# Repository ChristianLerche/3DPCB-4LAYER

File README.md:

# 3DPCB-4LAYER
Placeholder - don't use

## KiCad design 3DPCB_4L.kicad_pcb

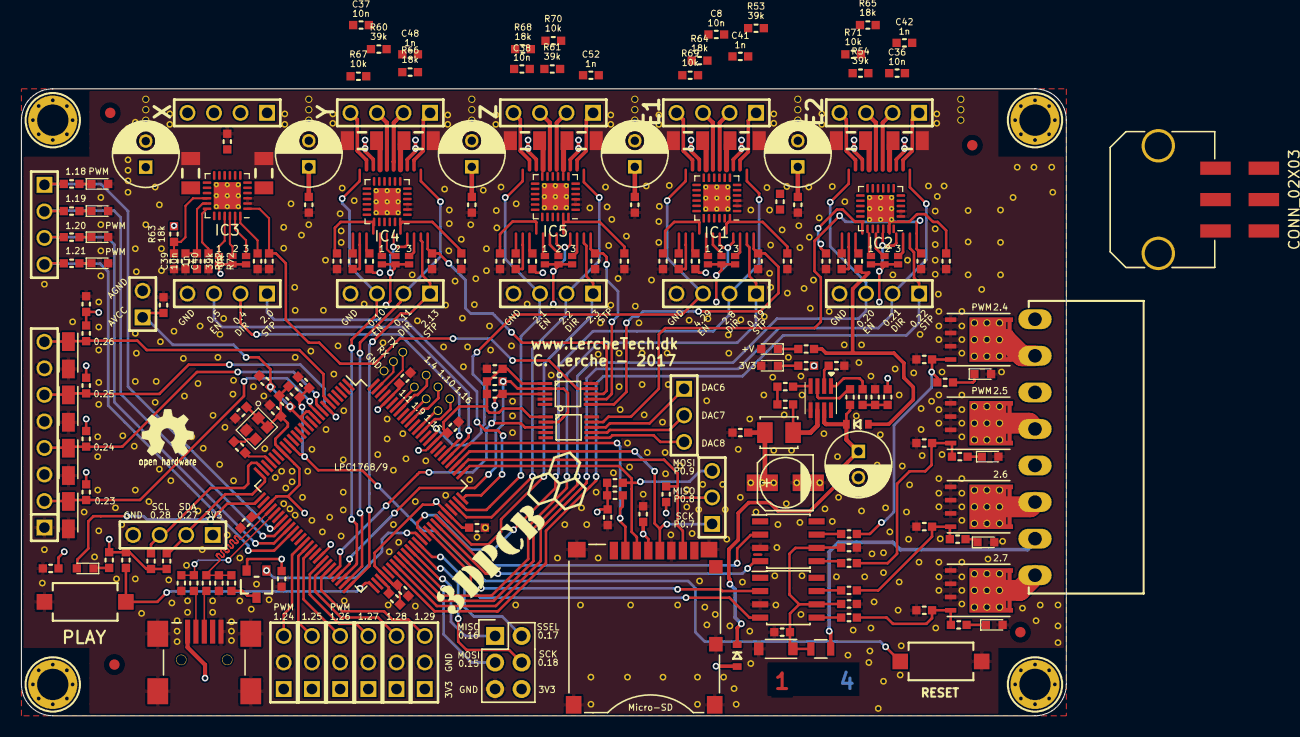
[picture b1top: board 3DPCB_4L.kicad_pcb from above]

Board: 4 copper layers, 100.0 x 60.0 mm, 224 parts (0 on the bottom side), 176 nets.

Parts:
C1, C2, C6, C12, C13, C14, C15, C16, C17, C19, C20, C21, C22, C23, C28, C29, C30, C31, C32, C33, C34, C35, C44, C45, C46, C47, C50, C51, C52, C53, C54, C64, C65, C67, C69, C71: 100n; Lerche_C0603
C3, C4, C7, C10: 10uF; TantalC_SizeA_EIA-3216_Reflow
C5, C9: 18p; Lerche_C0603
C8, C36, C37: 100nF; Lerche_C0603
C8#2, C36#2, C37#2, C38, C38#2, C39: 10n; Lerche_C0603
C11, C24, C25, C26, C27, C70: 100uF; C_Radial_D6.3_L11.2_P2.5
C18: 100pF; Lerche_C0603
C40, C41#2, C42#2, C48#2, C52#2: 1n; Lerche_C0603
C41, C42, C48, C55: 220n; Lerche_C0603
C43: 47uF; c_elec_5x5.8
C49: 1uF; Lerche_C0603
CONN1: USB_MINI; Lerche_MINI_USB
D1, D2, D3, D4, D6, D7, D8, D11, D12, D13, D14: LED; LED_0603
D5, D9: DIODESCH; Lerche_SOD323
D10: Vz10V/0.5W; SOD-123
FID1, FID2, FID3, FID4: FIDUCIAL; Lerche_Fiducial
IC1, IC2, IC3, IC4, IC5: STSPIN820; QFN-24-1EP_4x4mm_P0.5mm_EP2.6x2.6mm_ThermalVias
IC6: MP9943; Lerche_MP9943
J2, J3, J4, J5, J6, J7, J8, J9, J10, J11, J12, J13, J14, J15, J16: Lerche_2PsolderJumper
K1, K2, K3, K4, K5, K6, K8, K9: CONN_3; Lerche_3P_2.54mm
K7: CONN_3; Lerche_3P_1.27MM
L1: INDUCTOR; Lerche_R0603
L2: IHLP1212BZER2R2M11; Lerche_IHLP-1212BZ-11_Inductor
OSC1: QX2; Lerche_Oscillator_2.5x2.0mm
P1: CONN_8; Lerche_8P_2.54mm
P2: CONN_8; Lerche_8P_CONN_3,5mm
P3: CONN_01X02; Lerche_2P_2.54mm
P5, P6, P7, P9, P13: CONN_4; Lerche_4P_2.54mm
P8: CONN_02X03; Lerche_Molex_Microfit_0430450607
P11: CONN_3X2; Pin_Header_Straight_2x03
P12: CONN_3X2; Lerche_6P_1.6mm_2ROW
R1, R9, R18, R19, R25, R27, R41, R42, R43, R67, R69, R70, R71: 10k; Lerche_R0603
R2, R3, R4, R5, R6, R28: 1k; Lerche_R0603
R7, R8: 33R; Lerche_R0603
R10, R12, R13, R34: 4K7; Lerche_R0603
R11: 1k5; Lerche_R0603
R14, R15, R16, R20: 47k; Lerche_R0603
R17: 1k; R_0805
R21, R22, R23, R24, R29, R30, R31, R32, R33, R37: 0R05; Lerche_R1206
R26, R46, R47, R48, R72: 0R; Lerche_R0603
R35: 1M; Lerche_R0603
R36: 20R; Lerche_R0603
R38: 51k; Lerche_R0603
R39: 13k; Lerche_R0603
R40: 41k2; Lerche_R0603
R44, R45: 3k3; Lerche_R0603
R49, R50, R51, R52: 4k7; Lerche_R0603
R53, R54, R60, R61, R62: 39k; Lerche_R0603
R55: 5k8; Lerche_R0603
R56, R57, R58, R59: 10R; Lerche_R0603
R63, R64, R65, R66, R68: 18k; Lerche_R0603
U1, U4, U13, U16, U21, U22, U25: CONN_4_LERCHE; Lerche_4P_2.54mm
U2, U15: SPST_MOMENTARY; Lerche_SPST_ITEAD
U3: BSS84; Lerche_SOT23-3
U5, U7, U8, U24: IRFH5302; Lerche_PQFN_5x6B
U6: LPC1768_TQFP100; TQFP-100_14x14mm_Pitch0.5mm
U9, U11: TC4427; SOIC-8_3.9x4.9mm_Pitch1.27mm
U10: MICRO-SD; Lerche_Molex_502774-0891
U12, U23: MCP4728; Lerche_MSOP-10

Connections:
+3.3V: C6.1, C12.1, C13.1, C14.1, C15.1, C16.1, C19.2, C22.1, C23.1, C43.1, C44.1, C45.1, C46.1, C50.1, C64.1, J2.1, J3.1, J4.1, J5.1, J6.1, J7.1, J8.1, J9.1, J10.1, J11.1, J12.1, J13.1, J14.1, J15.1, J16.1, K1.1, K2.1, K3.1, K4.1, K5.1, K6.1, L1.1, L2.2, OSC1.1, OSC1.4, P11.6, R1.1, R2.1, R9.1, R10.1, R12.1, R13.1, R18.2, R19.2, R27.1, R28.1, R34.1, R40.1, R41.1, R42.1, R43.1, R44.1, R45.1, R63.2, R64.2, R65.2, R66.2, R68.2, U3.2, U6.19, U6.28, U6.42, U6.54, U6.71, U6.84, U6.96, U10.4, U12.1, U16.1, U23.1
+12V: C24.1, C25.1, C26.1, C27.1, C28.1, C29.1, C30.1, C31.1, C52.1, C53.1, C54.1, C69.1, C70.1, C71.1, D9.1, IC1.9, IC1.10, IC2.9, IC2.10, IC3.9, IC3.10, IC5.9, IC5.10, P8.2, R55.1
/P2.6_FET: P2.3, U8.3
/P2.7_FET: P2.1, U24.3
/PWM0_FET: P2.7, U5.3
/PWM1_FET: P2.5, U7.3
DAC_SCL: R19.1, U6.47, U12.2, U23.2
DAC_SDA: R18.1, U6.46, U12.3, U23.3
DIR1: IC3.20, U1.2, U6.81
DIR2: IC4.20, U6.49, U21.2
DIR3: IC5.20, U6.73, U22.2
DIR4: IC1.20, U6.65, U25.2
DIR5: IC2.20, U6.57, U13.2
EN1: R62.2, U1.3, U6.80
EN2: R60.2, U6.48, U21.3
EN3: R61.2, U6.74, U22.3
EN4: R53.2, U6.85, U25.3
EN5: R54.2, U6.58, U13.3
GND: C1.2, C2.2, C3.2, C4.2, C5.2, C6.2, C7.2, C8#2.2, C9.2, C10.2, C11.2, C12.2, C13.2, C14.2, C15.2, C16.2, C17.2, C19.1, C21.2, C22.2, C23.2, C24.2, C25.2, C26.2, C27.2, C28.2, C29.2, C30.2, C31.2, C32.2, C33.2, C34.2, C35.2, C36#2.2, C37#2.2, C38#2.2, C39.2, C40.1, C41.2, C41#2.1, C42.2, C42#2.1, C43.2, C44.2, C45.2, C46.2, C47.2, C48.2, C48#2.1, C49.2, C50.2, C51.2, C52#2.1, C55.2, C64.2, C65.2, C70.2, C71.2, CONN1.5, CONN1.Shie, D1.2, D2.2, D3.2, D4.2, D7.2, D8.2, D10.2, D11.2, D12.2, D13.2, D14.2, IC1.2, IC1.3, IC1.25, IC2.2, IC2.3, IC2.25, IC3.2, IC3.3, IC3.25, IC4.2, IC4.3, IC4.25, IC5.2, IC5.3, IC5.25, IC6.5, K1.2, K2.2, K3.2, K4.2, K5.2, K6.2, K7.3, OSC1.2, P1.1, P1.3, P1.5, P1.7, P3.2, P8.1, P8.4, P8.6, P11.5, R14.2, R15.2, R16.2, R20.2, R21.2, R22.2, R23.2, R24.2, R25.2, R26.2, R29.2, R30.2, R31.2, R32.2, R33.2, R37.2, R39.2, R46.2, R47.2, R48.2, R67.2, R69.2, R70.2, R71.2, R72.2, U1.4, U2.2, U5.2, U6.11, U6.15, U6.31, U6.41, U6.55, U6.72, U6.83, U6.97, U7.2, U8.2, U9.3, U10.6, U10.10, U10.11, U10.12, U10.13, U10.14, U11.3, U12.4, U12.10, U13.4, U15.2, U16.4, U21.4, U22.4, U23.4, U23.10, U24.2, U25.4
LED1: R3.2, U4.1, U6.32
LED2: R4.2, U4.2, U6.33
LED3: R5.2, U4.3, U6.34
LED4: R6.2, U4.4, U6.35
MISO1: P11.1, U6.61
MOSI1: P11.3, U6.60
MOSVCC: C21.1, C47.1, C49.1, D10.1, R17.2, U11.6
unnamed: C2.1, IC6.2
unnamed: C8.1, C8#2.1, IC1.17, R53.1
unnamed: C17.1, C35.1, L1.2, P3.1, U6.10, U6.12
unnamed: C18.1, OSC1.3
unnamed: C18.2, U6.22
unnamed: C20.1, R36.2
unnamed: C20.2, IC6.6, L2.1
unnamed: C36.1, C36#2.1, IC2.17, R54.1
unnamed: C37.1, C37#2.1, IC4.17, R60.1
unnamed: C38.1, C38#2.1, IC5.17, R61.1
unnamed: C39.1, IC3.17, R62.1
unnamed: C40.2, IC3.16, R63.1
unnamed: C41#2.2, IC1.16, R64.1
unnamed: C42#2.2, IC2.16, R65.1
unnamed: C48#2.2, IC4.16, R66.1
unnamed: C52.2, C52#2.2, IC5.16, R68.1
unnamed: CONN1.1, D5.1
unnamed: CONN1.2, R7.1
unnamed: CONN1.3, R8.1
unnamed: D1.1, R3.1
unnamed: D2.1, R4.1
unnamed: D3.1, R5.1
unnamed: D4.1, R6.1
unnamed: D6.1, R28.2
unnamed: D7.1, R2.2
unnamed: D8.1, R55.2
unnamed: D11.1, R50.2
unnamed: D12.1, R52.2
unnamed: D13.1, R49.2
unnamed: D14.1, R51.2
unnamed: IC1.4, IC1.5, IC1.6, R23.1
unnamed: IC1.7, P7.1
unnamed: IC1.8, P7.2
unnamed: IC1.11, P7.3
unnamed: IC1.12, P7.4
unnamed: IC1.13, IC1.14, IC1.15, R30.1
unnamed: IC1.18, R46.1
unnamed: IC1.21, J11.2
unnamed: IC1.22, J12.2
unnamed: IC1.23, J13.2
unnamed: IC1.24, R69.1
unnamed: IC2.4, IC2.5, IC2.6, R31.1
unnamed: IC2.7, P13.1
unnamed: IC2.8, P13.2
unnamed: IC2.11, P13.3
unnamed: IC2.12, P13.4
unnamed: IC2.13, IC2.14, IC2.15, R32.1
unnamed: IC2.18, R47.1
unnamed: IC2.21, J14.2
unnamed: IC2.22, J15.2
unnamed: IC2.23, J16.2
unnamed: IC2.24, R71.1
unnamed: IC3.4, IC3.5, IC3.6, R33.1
unnamed: IC3.7, P9.1
unnamed: IC3.8, P9.2
unnamed: IC3.11, P9.3
unnamed: IC3.12, P9.4
unnamed: IC3.13, IC3.14, IC3.15, R37.1
unnamed: IC3.18, R72.1
unnamed: IC3.21, J2.2
unnamed: IC3.22, J3.2
unnamed: IC3.23, J4.2
unnamed: IC3.24, R25.1
unnamed: IC4.4, IC4.5, IC4.6, R21.1
unnamed: IC4.7, P5.1
unnamed: IC4.8, P5.2
unnamed: IC4.11, P5.3
unnamed: IC4.12, P5.4
unnamed: IC4.13, IC4.14, IC4.15, R24.1
unnamed: IC4.18, R48.1
unnamed: IC4.21, J5.2
unnamed: IC4.22, J6.2
unnamed: IC4.23, J7.2
unnamed: IC4.24, R67.1
unnamed: IC5.4, IC5.5, IC5.6, R22.1
unnamed: IC5.7, P6.1
unnamed: IC5.8, P6.2
unnamed: IC5.11, P6.3
unnamed: IC5.12, P6.4
unnamed: IC5.13, IC5.14, IC5.15, R29.1
unnamed: IC5.18, R26.1
unnamed: IC5.21, J8.2
unnamed: IC5.22, J9.2
unnamed: IC5.23, J10.2
unnamed: IC5.24, R70.1
unnamed: IC6.1, R38.1
unnamed: IC6.3, R35.1
unnamed: IC6.4, R36.1
unnamed: R11.1, U3.3
unnamed: R14.1, R49.1, R56.2, U5.1
unnamed: R15.1, R50.1, R58.2, U7.1
unnamed: R16.1, R51.1, R57.2, U8.1
unnamed: R20.1, R52.1, R59.2, U24.1
unnamed: R38.2, R39.1, R40.2
unnamed: R56.1, U9.7
unnamed: R57.1, U11.7
unnamed: R58.1, U9.5
unnamed: R59.1, U11.5
P1.1: P12.2, U6.94
P1.4: P12.1, U6.93
P1.9: P12.4, U6.91
P1.10: P12.3, U6.90
P1.15: P12.6, U6.88
P1.16: P12.5, U6.87
P2.4: U6.69, U9.2
P2.5: U6.68, U9.4
P2.6: U6.67, U11.2
P2.7: U6.66, U11.4
PLAY: R27.2, U6.51, U15.1
PLAY_LED: D6.2, U6.26
RX_0: K7.2, U6.99
SCK1: P11.4, U6.62
SCL: R45.2, U6.24, U16.3
SCON: U3.1, U6.64
SDA: R44.2, U6.25, U16.2
SD_CS: R43.2, U6.79, U10.2
SD_MISO: K8.2, R42.2, U6.77, U10.7
SD_MOSI: K8.3, R41.2, U6.76, U10.3
SD_SCK: K8.1, U6.78, U10.5
SSEL1: P11.2, U6.63
STP1: IC3.19, U1.1, U6.75
STP2: IC4.19, U6.50, U21.1
STP3: IC5.19, U6.70, U22.1
STP4: IC1.19, U6.59, U25.1
STP5: IC2.19, U6.56, U13.1
TH1: C3.1, P1.2, R34.2, U6.9
TH2: C4.1, P1.4, R10.2, U6.8
TH3: C7.1, P1.6, R12.2, U6.7
TH4: C10.1, P1.8, R13.2, U6.6
TX_0: K7.1, U6.98
USB_D+: C5.1, R8.2, R11.2, U6.29
USB_D-: C9.1, R7.2, U6.30
VDCVDC: C11.1, D5.2, D9.2, IC6.7, R35.2
VREF1: C51.1, IC3.1, U23.9
VREF2: C32.1, IC4.1, U23.8
VREF3: C33.1, IC5.1, U23.7
VREF4: C34.1, IC1.1, U23.6
VREF5: C65.1, IC2.1, U12.9
VREF6: K9.1, U12.8
VREF7: K9.2, U12.7
VREF8: K9.3, U12.6
V_MOSFET: P2.2, P2.4, P2.6, P2.8, P8.3, P8.5, R17.1
X-MAX: K2.3, U6.39
X-MIN: K1.3, U6.38
Y-MAX: K4.3, U6.43
Y-MIN: K3.3, U6.40
Z-MAX: K6.3, U6.45
Z-MIN: K5.3, U6.44
~ISP: R9.2, U6.53
~RESET: C1.1, R1.2, U2.1, U6.17

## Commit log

2015-08-20 First upload, PCB not yet finished
2015-08-20 Trying MP9943 DC to DC
2015-08-20 Needs to make MP9943 footprint for PCB
2015-08-24 PCB routed, needs specific BOM
2015-08-24 Added 3D image
2015-09-14 All PCB is routed - PCB sent to production
2015-09-16 Removed soldermask from stackup-info
2015-10-28 All files added - Hardware is NOT tested yet
2015-10-28 Changed placement of WEEE symbol, set layers visible
2016-08-21 Added LercheTech library
2016-10-31 Updated
    local repository + minor change to allow 24V on MOSFET drivers.
2016-11-16 Changing parts.
    DONT USE THIS NOW.
2016-11-17 Added library and .pretty footprints to project.
    Added library and .pretty footprints to project.
2016-11-17 Removing files
    .
2016-11-17 Updated PCB
    Updated PCB, splitting power for MOSFETs and motor-drivers.
2016-11-18 Minor changes DONT USE NOW
    Do not use this right now, changes are still coming in.
2016-12-07 Branching to follow Smoothieboard V1.1
    Update, following Smoothieboard V1.1
2016-12-07 Added A5984 to schematic
    Added A5984 to schematic
2016-12-07 First A5984 in place - DO NOT USE
    First A5984 in place - DO NOT USE
2016-12-07 DONT USE NOW
    Still working on PCB.
2016-12-08 Wired all connections with A5984 on PCB
    UNTESTED - Do not use now.
2016-12-09 Moved vias around
    Moved vias around
2016-12-09 Still doing work
    Still doing work
2016-12-09 Spokes on high current path removed.
    Spokes on high current path removed.
2016-12-14 Adding resistor to ROSC - DONT USE
    DONT USE YET
2016-12-16 Adding resistor to ROSC - Tracing it.
    Adding resistor to ROSC - Tracing it.
2017-01-03 BGA testing
    BGA testing
2017-01-12 Removing parts
    Removing parts
2017-01-12 Added smaller parts
    Added LEDs to MOSFETs, adding AVCC and AGND connector
2017-02-06 Updating- DO NOT USE NOW
    Updating- DO NOT USE NOW
2017-02-06 fresh fork
    fresh fork
2017-02-06 Started SODIMM version
2017-02-06 Starting the work
2017-02-28 A4982/A5984 compatible
    Now it's possible to use both stepper drivers. Everything else is the
    same. PCB's will be produced within a short timespan.
2017-03-01 TEsting routing
    Testing routing options, like differential, length matching and so on.
    Is not routed yet.
2017-03-01 Smaller traces, length matching USB
    Smaller traces, length matching USB
2017-03-02 Rewiring some things.
    Rewiring some things.
2017-03-13 Minor adjustments.
    Getting ready to order boards now.
2017-03-16 Updated pinheader
    Updated pinheader
2017-03-17 Touch-up on some parts, silkscreen and logo
    Should be ready for production soon.
2017-08-18 Update
    Update
2018-02-21 Working files.
    Tested, working!
2020-11-19 Startup
2020-11-19 Changed names for SPI pinout
    Added PDF of schematic.
2020-11-19 Fixed pinout names for SPI breakout
    Fixed pinout, added schematic in PDF.
2020-11-24 Working on the PCB
2022-03-06 Updated with KiCAD 6.0
2022-04-28 Updated with KiCAD 6.0.4
2022-06-26 Minor changes
